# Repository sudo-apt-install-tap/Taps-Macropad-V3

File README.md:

<div align="center">

<h1>
  <b>
    Taps Macropad V3
  </b> 
</h1>

<h3> <b> A 16 Key + 2 Rotatory Encoder Macropad! </b> </h3>

</div>

## **Overview**

A Macropad With 16 Keys And 2 Rotatory Encoders!

### Why?
I wanted a macropad better than my [current one!](https://github.com/sudo-apt-install-tap/Taps-ez-copy-n-paste).

### How?
Use the firmware in [FIRMWARE](firmware) . I've used circuitpy and kmk to do it!

## CAD
CAD files are available at [CAD](https://cad.onshape.com/documents/8e68ca6e98fe2a8c06c64278/w/6cdda3ae126c898349003511/e/612b83dc1028b3e711fd50c7?renderMode=0&uiState=69b8ff27c4cd638791be8287)

## Images
<div align="center">

<br> Full render<br>

---

<br> PCB

---

<br> Sch

---

<br> 3D Viewer

---

<h2>Build Images:</h2>

<br> Full Assembly

---

<br> Back Side Of PCB

---

<br> Bodged Art Of Hardware

---
</div>

## Demo Video Hosted On YouTube

[Demo #003 V3](https://youtu.be/LXwYWxPGB4U)

## BOM

| Name             | Purpose           | Cost (USD) | Qty | Total (USD) | Link | Distributor  |
|-----------------|-----------------|------------|-----|-------------|------|-------------|
| Rotatory Encoders | Rotatory Encoders | $0.00      | 2   | $0.00       | -    | Self sourced |
| RP2040 Zero      | MCU               | $0.00      | 1   | $0.00       | -    | SelfSourced |
| Keys and Diodes  | Diodes and keys   | $11.00     | 1   | $11.00      | -    | Stackskb    |
| PCB              | PCB               | $13.00     | 1   | $13.00      | -    | JLC         |

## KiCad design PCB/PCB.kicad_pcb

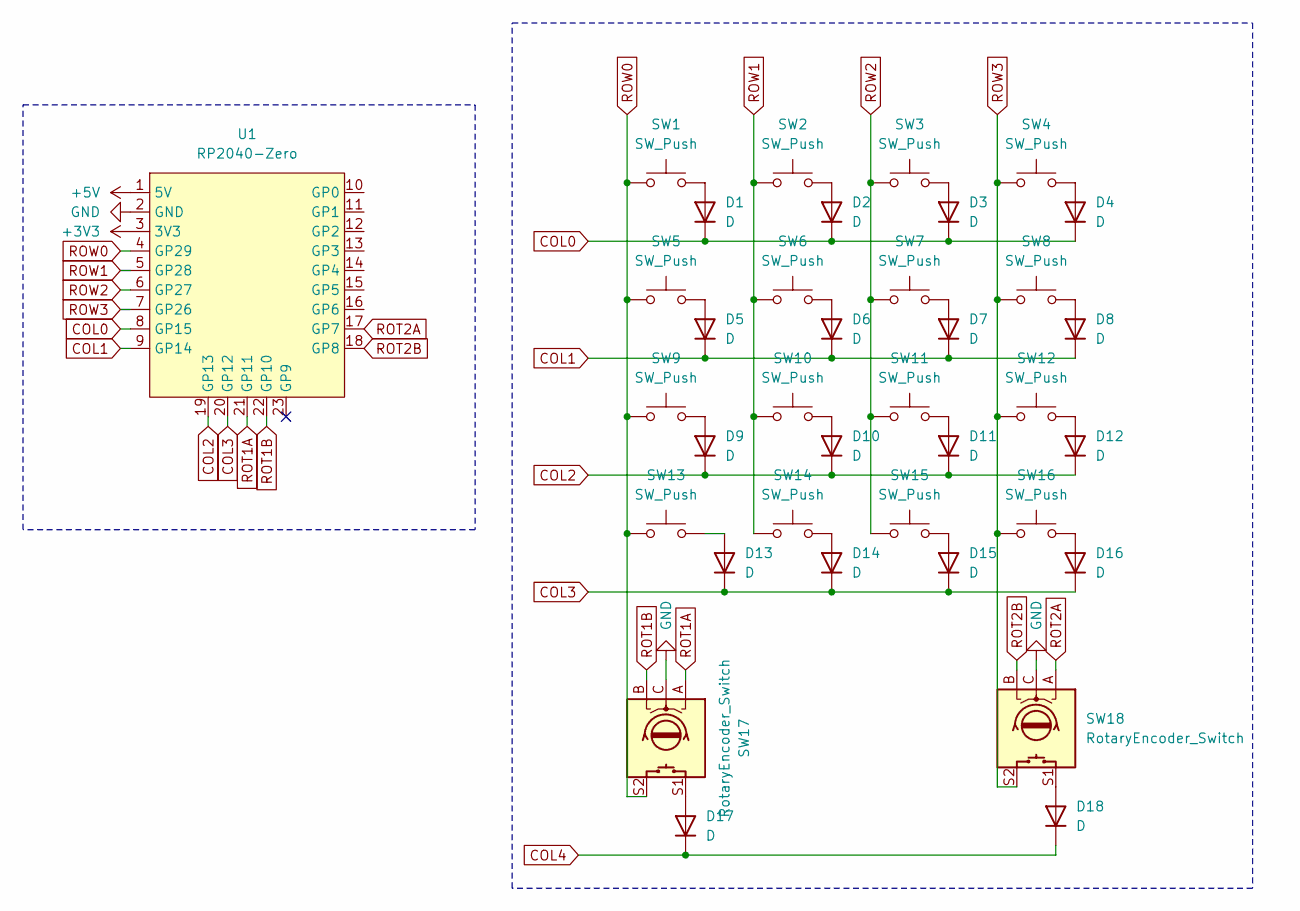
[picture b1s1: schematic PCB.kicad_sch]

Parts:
D1, D2, D3, D4, D5, D6, D7, D8, D9, D10, D11, D12, D13, D14, D15, D16, D17, D18: D; D_SOD-123
SW1, SW2, SW3, SW4, SW5, SW6, SW7, SW8, SW9, SW10, SW11, SW12, SW13, SW14, SW15, SW16: SW_Push; SW_Hotswap_Kailh_MX
SW17, SW18: RotaryEncoder_Switch; RotaryEncoder_Alps_EC11E-Switch_Vertical_H20mm
U1: RP2040-Zero; RP2040 Zero

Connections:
+3V3: U1.3 (3V3); also elsewhere on the board
+5V: U1.1 (5V); also elsewhere on the board
COL0: D1.1 (K), D2.1 (K), D3.1 (K), D4.1 (K), U1.8 (GP15)
COL1: D5.1 (K), D6.1 (K), D7.1 (K), D8.1 (K), U1.9 (GP14)
COL2: D9.1 (K), D10.1 (K), D11.1 (K), D12.1 (K), U1.19 (GP13)
COL3: D13.1 (K), D14.1 (K), D15.1 (K), D16.1 (K), U1.20 (GP12)
COL4: D17.1 (K), D18.1 (K)
GND: SW17.C, SW18.C, U1.2 (GND); also elsewhere on the board
unnamed: D1.2 (A), SW1.2
unnamed: D2.2 (A), SW2.2
unnamed: D3.2 (A), SW3.2
unnamed: D4.2 (A), SW4.2
unnamed: D5.2 (A), SW5.2
unnamed: D6.2 (A), SW6.2
unnamed: D7.2 (A), SW7.2
unnamed: D8.2 (A), SW8.2
unnamed: D9.2 (A), SW9.2
unnamed: D10.2 (A), SW10.2
unnamed: D11.2 (A), SW11.2
unnamed: D12.2 (A), SW12.2
unnamed: D13.2 (A), SW13.2
unnamed: D14.2 (A), SW14.2
unnamed: D15.2 (A), SW15.2
unnamed: D16.2 (A), SW16.2
unnamed: D17.2 (A), SW17.S1
unnamed: D18.2 (A), SW18.S1
ROT1A: SW17.A, U1.21 (GP11)
ROT1B: SW17.B, U1.22 (GP10)
ROT2A: SW18.A, U1.17 (GP7)
ROT2B: SW18.B, U1.18 (GP8)
ROW0: SW1.1, SW5.1, SW9.1, SW13.1, SW17.S2, U1.4 (GP29)
ROW1: SW2.1, SW6.1, SW10.1, SW14.1, U1.5 (GP28)
ROW2: SW3.1, SW7.1, SW11.1, SW15.1, U1.6 (GP27)
ROW3: SW4.1, SW8.1, SW12.1, SW16.1, SW18.S2, U1.7 (GP26)

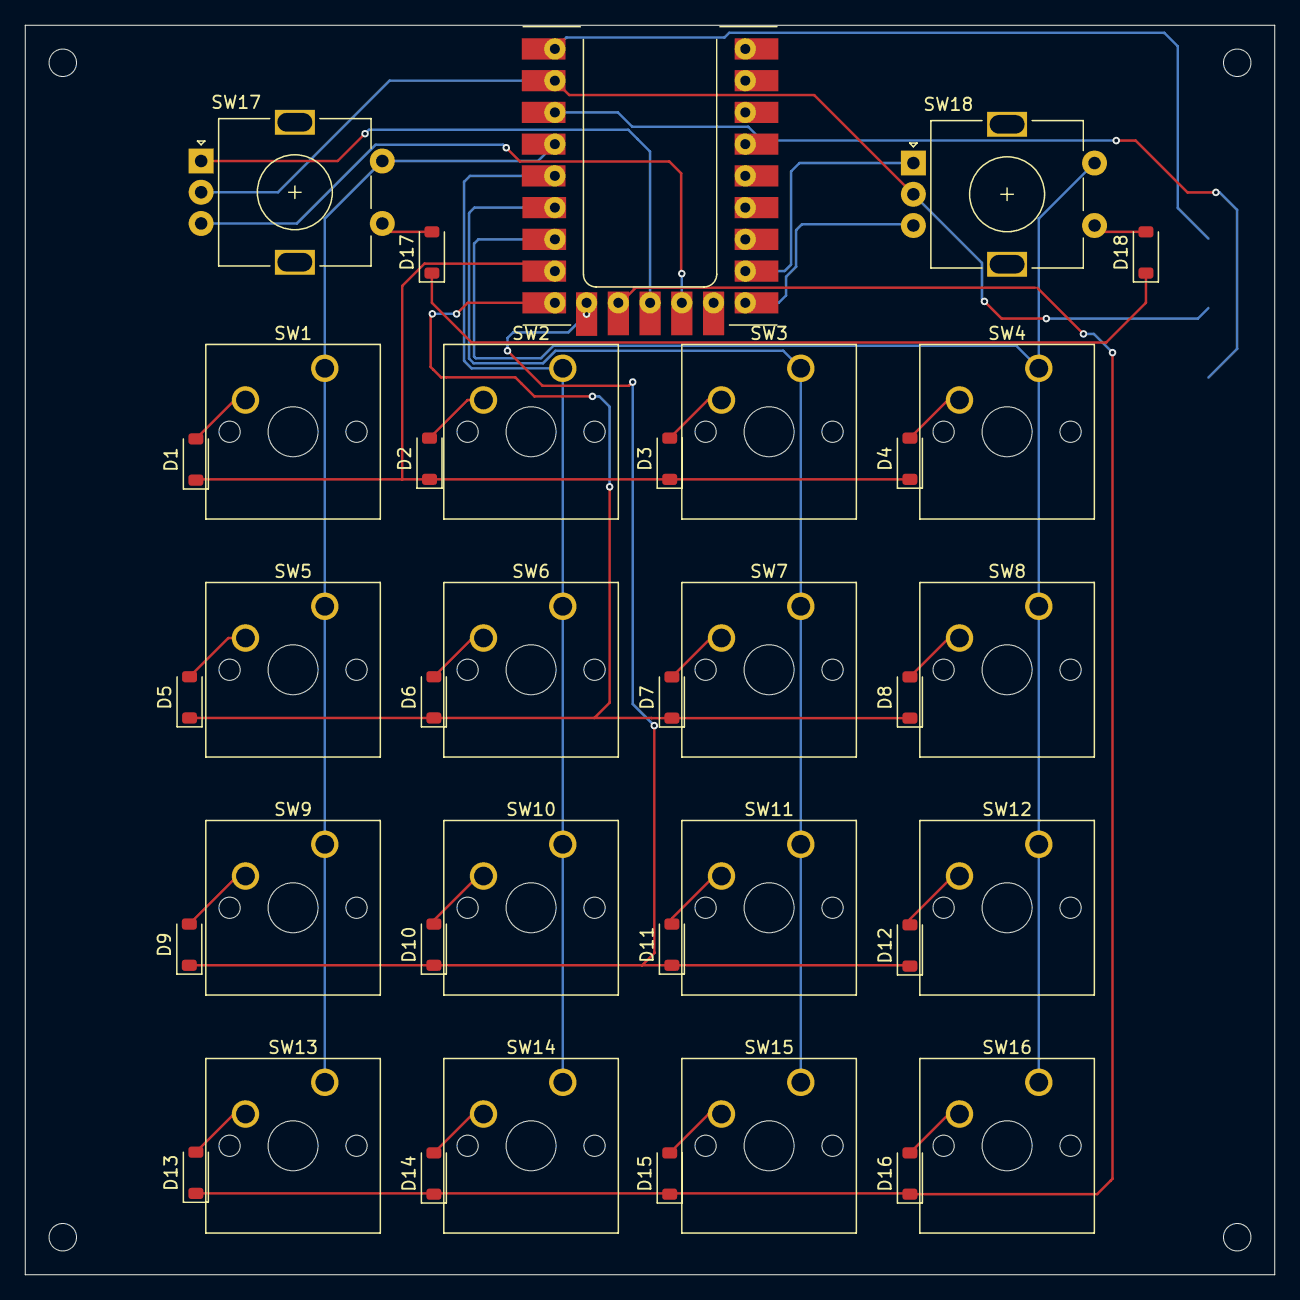
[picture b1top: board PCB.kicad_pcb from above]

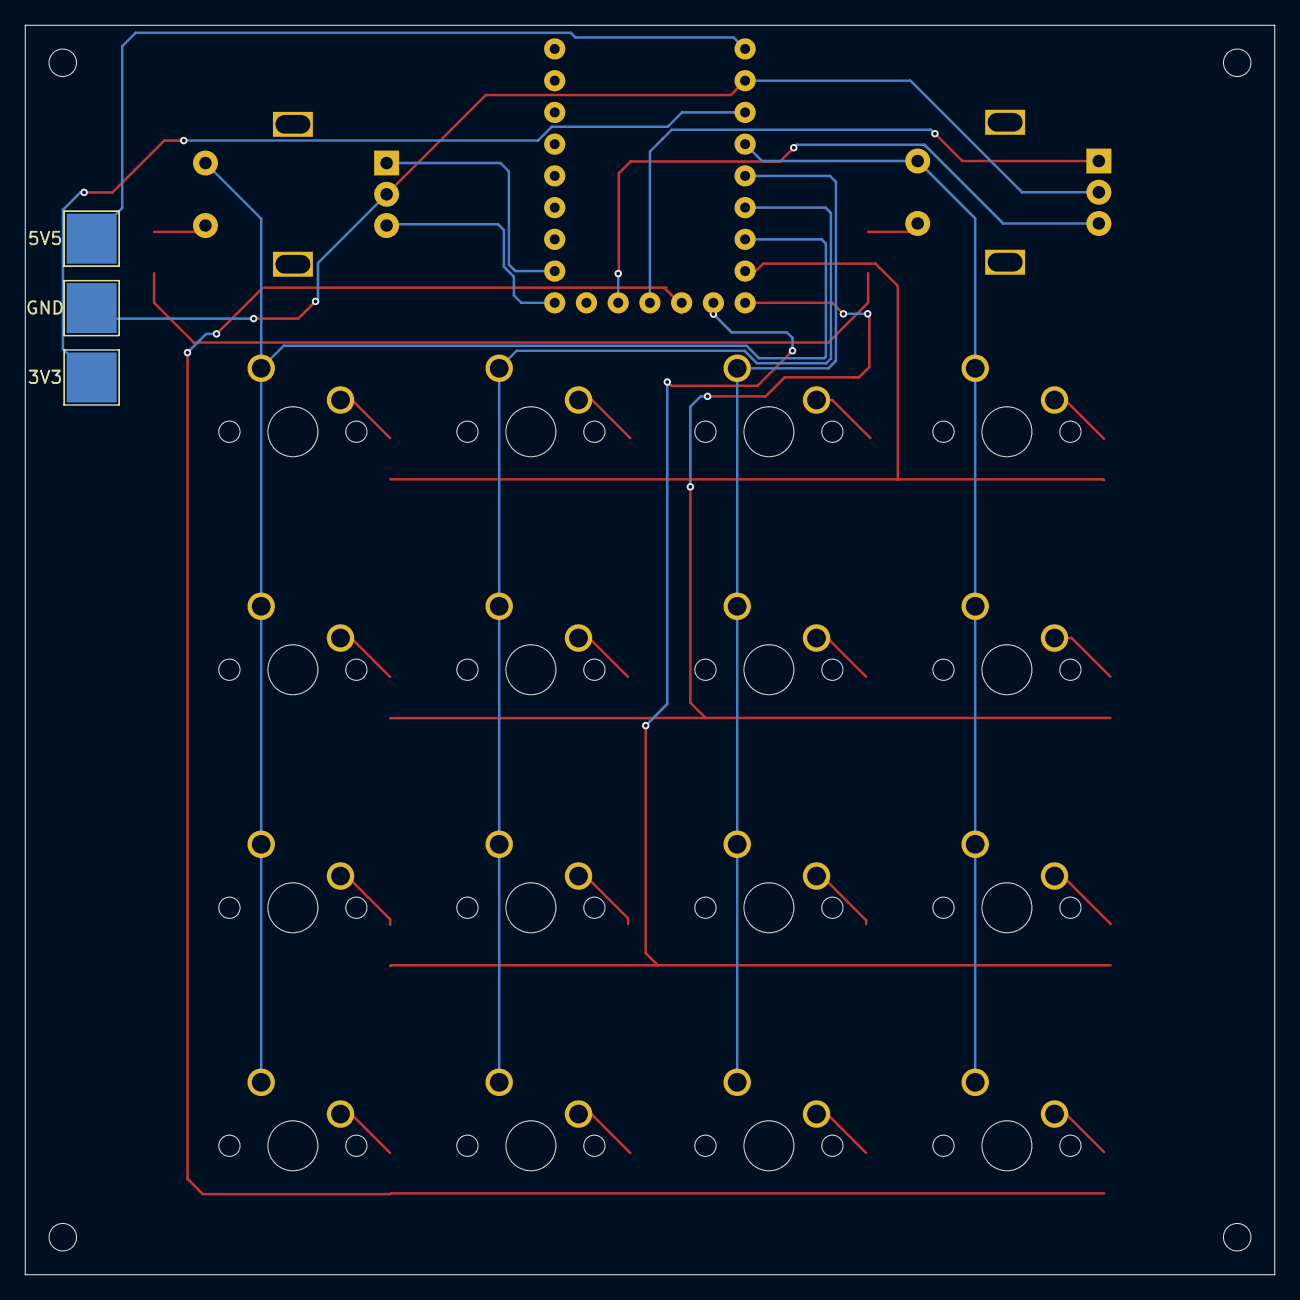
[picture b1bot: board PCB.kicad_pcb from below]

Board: 2 copper layers, 100.0 x 100.0 mm, 40 parts (3 on the bottom side), 34 nets.

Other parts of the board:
3V3, 5V5: TestPoint_Pad_4.0x4.0mm
GND: TestPoint_Pad_4.0x4.0mm

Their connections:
+3V3: 3V3.1; also elsewhere on the board
+5V: 5V5.1; also elsewhere on the board
GND: GND.1; also elsewhere on the board

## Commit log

2026-03-17 Add README for Taps Macropad V3
    Added detailed information about the Taps Macropad V3, including an overview, reasons for creation, firmware usage, CAD files, and images.
2026-03-17 Added /Images
2026-03-17 added basic firmware
2026-03-17 Update README to include BOM section
    Added BOM section with components and costs.
2026-04-01 Remove unnecessary comments and clean up code
2026-05-02 Added Case STEPs
2026-05-13 added images and videos
2026-05-13 Update README.md
    Added images and shi
